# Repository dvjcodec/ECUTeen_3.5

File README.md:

# ECUTeen_3.5 rev.A (not tested!)

Stand Alone ECU with Teensy 3.5

On the board:
- 4 injection chanels
- 4 ignition chanels (for active coils)
- 2 high current PWM chanels
- IDLE out
- BOOST out
- stepper motor 
- 3x low current outs (FAN, FUEL, LC1)
- BlueTooth connector
- Clutch control
- tachometer out
- 5V power supply with LM2596
- 2x O2 sensor input
- CAN
- inlet air temperature sensor input
- coolant temperature sensor input
- throttle position sensor input
- 2x HALL input or VR
- MAP sensor 3bar

## Firmware

Designed for firmware
[Speeduino](https://speeduino.com/forum/viewtopic.php?f=13&t=1593)

## License

[CC BY-NC 3.0](https://creativecommons.org/licenses/by-nc/3.0/)

## Authors

Krzysztof Dymianiuk @ Seaside Customs Garage
http://www.garage.seasidecustoms.com

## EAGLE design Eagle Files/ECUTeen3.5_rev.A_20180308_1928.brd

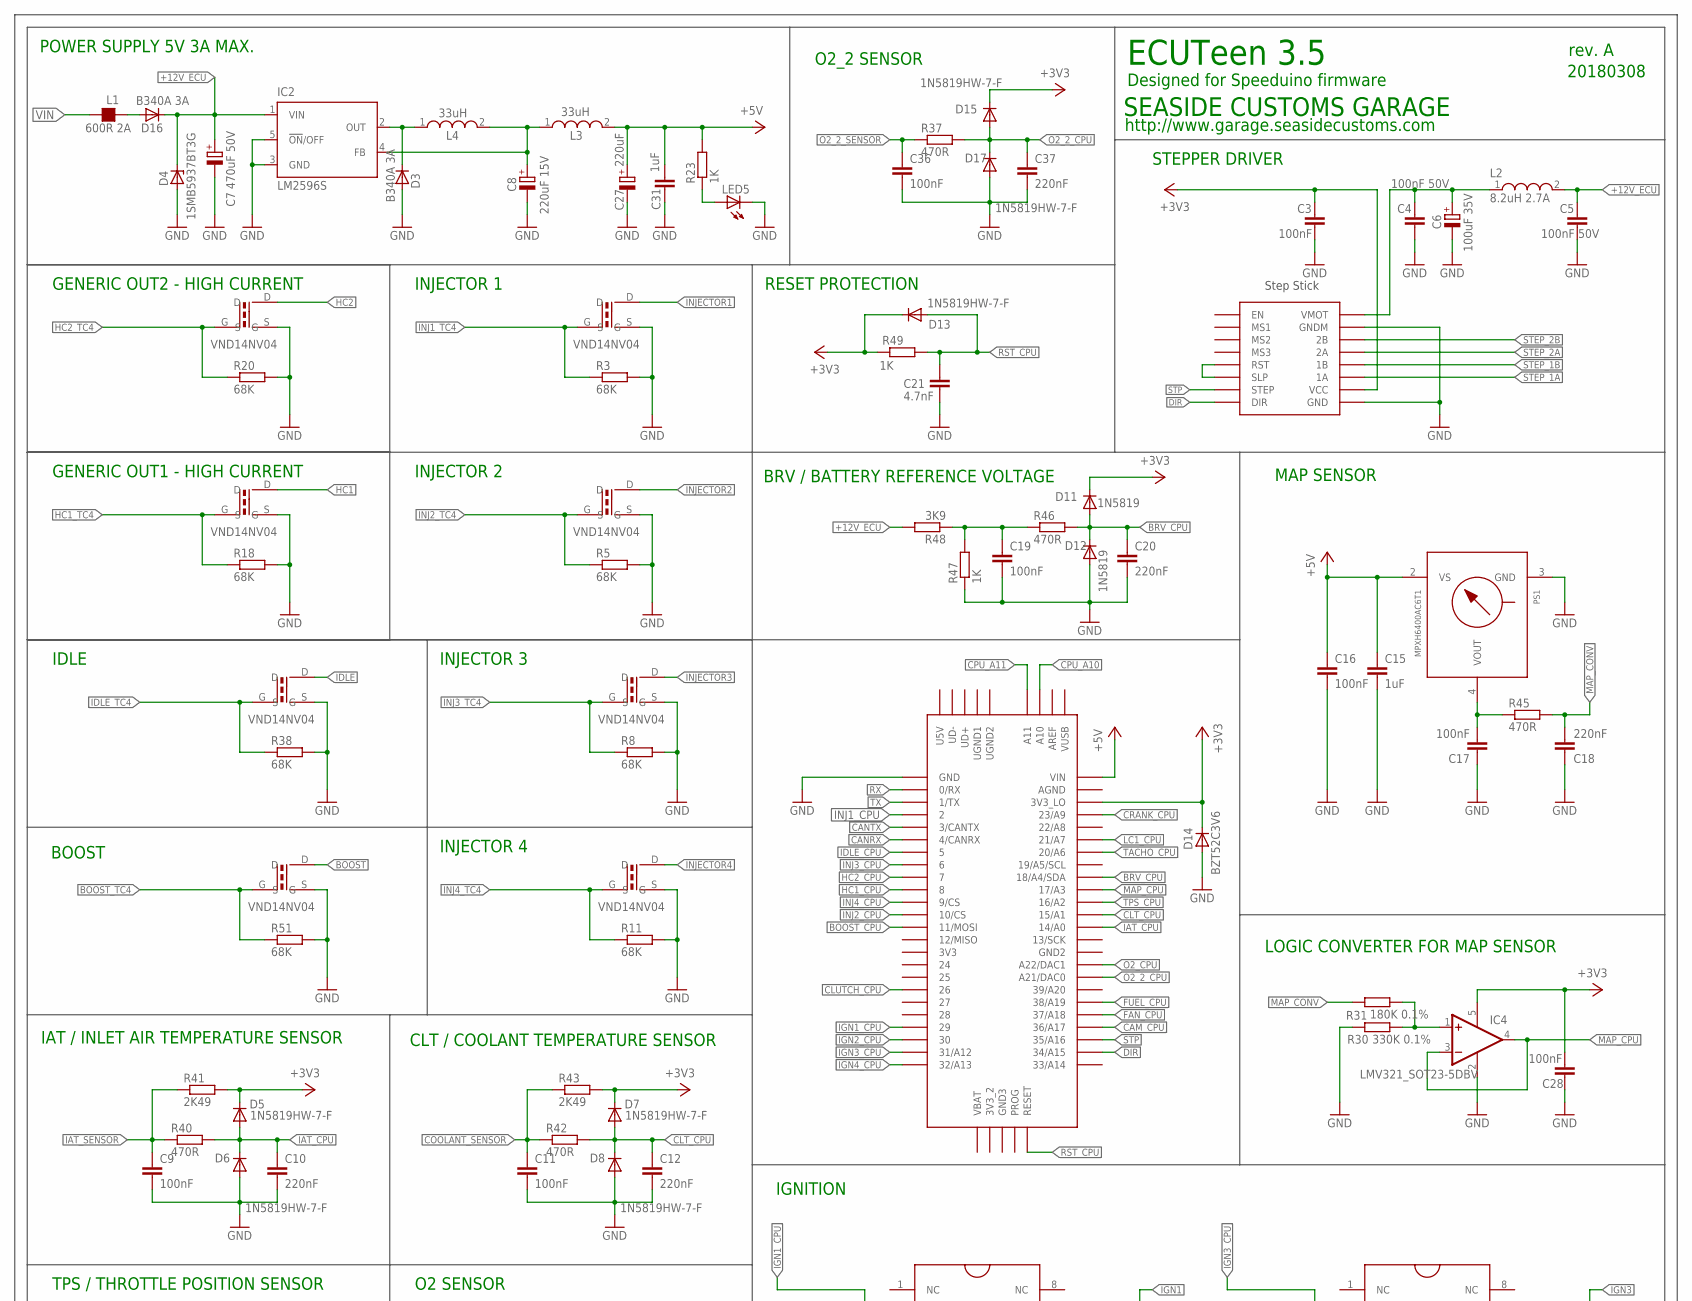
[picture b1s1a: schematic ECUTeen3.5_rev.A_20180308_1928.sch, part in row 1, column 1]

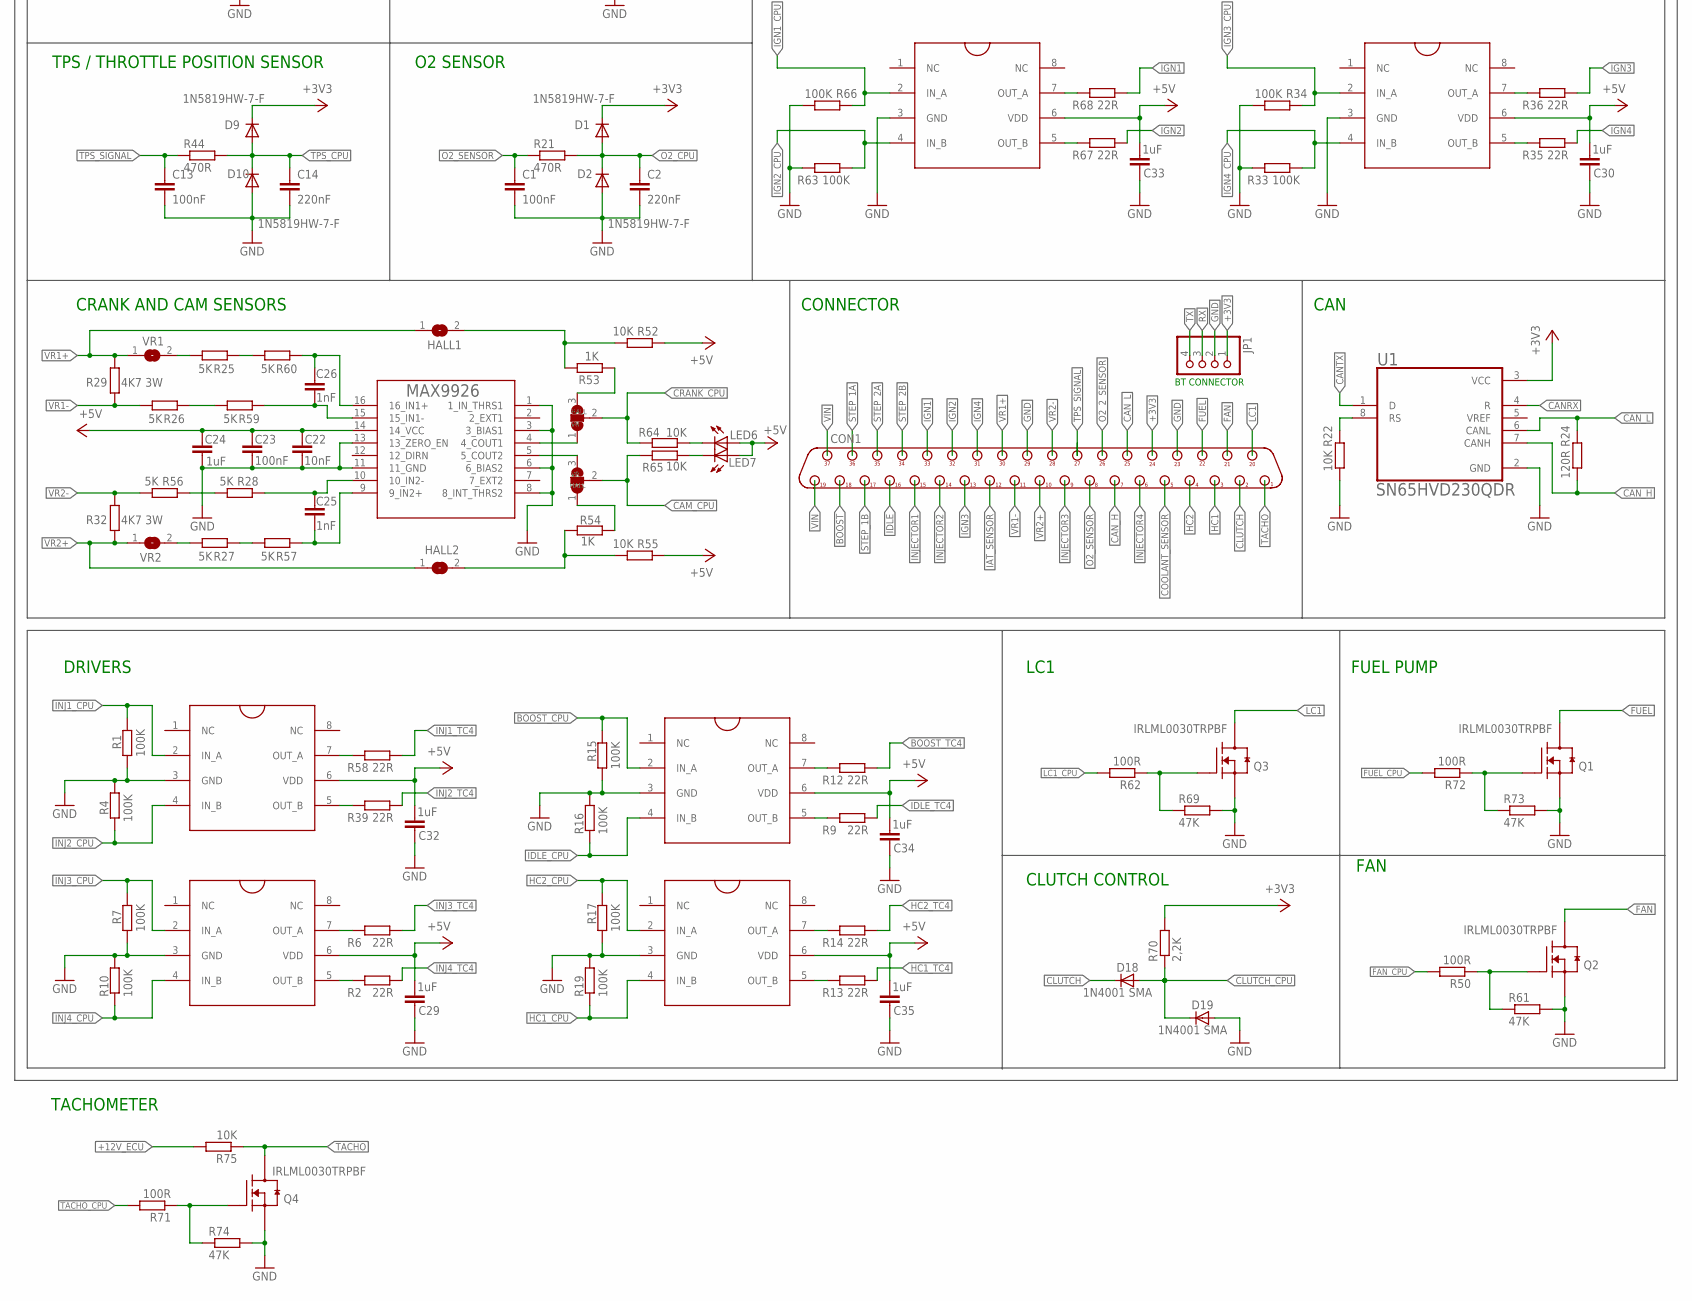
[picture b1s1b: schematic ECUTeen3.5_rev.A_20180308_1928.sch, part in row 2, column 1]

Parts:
C1, C3, C9, C11, C13, C16, C17, C19, C23, C28, C36: 100nF; C0805
C2, C10, C12, C14, C18, C20, C37: 220nF; C0805
C4, C5: 100nF 50V; C0805
C6: 100uF 35V; PANASONIC_D
C7: 470uF 50V; PANASONIC_D
C8: 220uF 15V; PANASONIC_D
C15, C24, C29, C30, C31, C32, C33, C34, C35: 1uF; C0805
C21: 4.7nF; C0805
C22: 10nF; C0805
C25, C26: 1nF; C0805
C27: 220uF; PANASONIC_D
CON1: DB37M/90; D-37M/90
D1, D2, D5, D6, D7, D8, D9, D10, D13, D15, D17: 1N5819HW-7-F; SOD123
D3, D16: B340A 3A; DO214AC
D4: 1SMB5937BT3G; SMB
D11, D12: 1N5819; SOD123
D14: BZT52C3V6; SOD123
D18, D19: 1N4001 SMA; DO214AC
IC2: LM2596S; TO263-5
IC4: LMV321_SOT23-5DBV; SOT23-5
JMP1, JMP2: SJ2W; SJ_2
JP1: PINHD-1X4; 1X04
L1: 600R 2A; L1206
L2: 8.2uH 2.7A; WE-PD_7332/7345_PLASTIC_BASE
L3, L4: 33uH; WE-LHMI_7030/7050
LED5, LED6, LED7: LEDCHIP-LED0805; CHIP-LED0805
PS1: MPXH6400AC6T1; 1317A
Q1, Q2, Q3, Q4: IRLML0030TRPBF; SOT95P280X135-3N
R1, R4, R7, R10, R15, R16, R17, R19, R33, R34, R63, R66: 100K; R0805
R2, R6, R9, R12, R13, R14, R39, R58: 22R; R0805
R3, R5, R8, R11, R18, R20, R38, R51: 68K; R0805
R21, R37, R40, R42, R44, R45, R46: 470R; R0805
R22, R52, R55, R64, R65, R75: 10K; R0805
R23, R47, R49, R53, R54: 1K; R0805
R24: 120R; R0805
R25, R26, R27, R28, R56, R57, R59, R60: 5K; R0805
R29, R32: 4K7 3W; R2512
R30: 330K 0.1%; R0805
R31: 180K 0.1%; R0805
R35, R36, R67, R68: 22R; M1206
R41, R43: 2K49; R0805
R48: 3K9; R0805
R50, R62, R71, R72: 100R; R0805
R61, R69, R73, R74: 47K; R0805
R70: 2,2K; R0805
SJ3: VR2; SJ
SJ4: VR1; SJ
SJ5: HALL2; SJ
SJ6: HALL1; SJ
STEPSTICK-X: STEP-STICK
U1: SN65HVD230QDR; SOIC127P600X175-8N
U$1: TEENSY_3.5/3.6
U$2, U$3, U$4, U$5, U$6, U$8, U$12, U$13: DPAK_N-CHANNEL_MOSFET
U$7, U$9, U$11, U$14, U$15, U$16: TC427SO-8; SO-8
U$10: MAX9926; QSOP16

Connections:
+3V3: C3.1, C28.2, CON1.24, D1.C, D5.C, D7.C, D9.C, D11.C, D13.C, D14.C, D15.C, IC4.5 (V+), JP1.1, R41.2, R43.2, R49.1, R70.2, STEPSTICK-X.VCC, U1.3 (VCC), U$1.3V3_LO
+5V: C15.1, C16.1, C22.1, C23.1, C24.1, C27.+, C29.2, C30.2, C31.1, C32.2, C33.2, C34.2, C35.2, L3.2, LED6.A, LED7.A, PS1.2 (VS), R23.2, R52.1, R55.1, U$1.VIN, U$7.6 (VDD), U$9.6 (VDD), U$10.14 (14_VCC), U$11.6 (VDD), U$14.6 (VDD), U$15.6 (VDD), U$16.6 (VDD)
+12V_ECU: C5.1, C7.+, D4.C, D16.C, IC2.1 (VIN), L2.2, R48.2, R75.2
BOOST: CON1.18, U$13.D
BOOST_CPU: R15.2, U$1.11/MOSI, U$15.2 (IN_A)
BOOST_TC4: R12.2, R51.1, U$13.G
BRV_CPU: C20.1, D11.A, D12.C, R46.2, U$1.18/A4/SDA
CAM_CPU: JMP2.2, R65.1, U$1.36/A17
CANRX: U1.4 (R), U$1.4/CANRX
CANTX: U1.1 (D), U$1.3/CANTX
CAN_H: CON1.7, R24.2, U1.7 (CANH)
CAN_L: CON1.25, R24.1, U1.6 (CANL)
CLT_CPU: C12.1, D7.A, D8.C, R42.2, U$1.15/A1
CLUTCH: CON1.2, D18.C
CLUTCH_CPU: D18.A, D19.C, R70.1, U$1.26
COOLANT_SENSOR: C11.1, CON1.5, R42.1, R43.1
CPU_A10: U$1.A10
CPU_A11: U$1.A11
CRANK_CPU: JMP1.2, R64.1, U$1.23/A9
DIR: STEPSTICK-X.DIR, U$1.34/A15
FAN: CON1.21, Q2.3 (D)
FAN_CPU: R50.2, U$1.37/A18
FUEL: CON1.22, Q1.3 (D)
FUEL_CPU: R72.2, U$1.38/A19
GND: C1.2, C2.2, C3.2, C4.2, C5.2, C6.-, C7.-, C8.-, C9.2, C10.2, C11.2, C12.2, C13.2, C14.2, C15.2, C16.2, C17.1, C18.1, C19.2, C20.2, C21.2, C22.2, C23.2, C24.2, C27.-, C28.1, C29.1, C30.1, C31.2, C32.1, C33.1, C34.1, C35.1, C36.2, C37.2, CON1.23, CON1.29, D2.A, D3.A, D4.A, D6.A, D8.A, D10.A, D12.A, D14.A, D17.A, D19.A, IC2.3 (GND), IC2.5 (!ON!/OFF), IC4.2 (V-), JP1.2, LED5.C, PS1.3 (GND), Q1.2 (S), Q2.2 (S), Q3.2 (S), Q4.2 (S), R1.1, R3.2, R4.1, R5.2, R7.1, R8.2, R10.1, R11.2, R15.1, R16.1, R17.1, R18.2, R19.1, R20.2, R22.2, R30.1, R33.1, R34.2, R38.2, R47.1, R51.2, R61.2, R63.1, R66.2, R69.2, R73.2, R74.2, STEPSTICK-X.GND, STEPSTICK-X.GNDM, U1.2 (GND), U$1.GND, U$2.S, U$3.S, U$4.S, U$5.S, U$6.S, U$7.3 (GND), U$8.S, U$9.3 (GND), U$10.1 (1_IN_THRS1), U$10.3 (3_BIAS1), U$10.6 (6_BIAS2), U$10.8 (8_INT_THRS2), U$10.11 (11_GND), U$10.13 (13_ZERO_EN), U$11.3 (GND), U$12.S, U$13.S, U$14.3 (GND), U$15.3 (GND), U$16.3 (GND)
HC1: CON1.3, U$3.D
HC1_CPU: R19.2, U$1.8, U$16.4 (IN_B)
HC1_TC4: R13.2, R18.1, U$3.G
HC2: CON1.4, U$2.D
HC2_CPU: R17.2, U$1.7, U$16.2 (IN_A)
HC2_TC4: R14.2, R20.1, U$2.G
IAT_CPU: C10.1, D5.A, D6.C, R40.2, U$1.14/A0
IAT_SENSOR: C9.1, CON1.12, R40.1, R41.1
IDLE: CON1.16, U$5.D
IDLE_CPU: R16.2, U$1.5, U$15.4 (IN_B)
IDLE_TC4: R9.2, R38.1, U$5.G
IGN1: CON1.33, R68.2
IGN1_CPU: R66.1, U$1.29, U$9.2 (IN_A)
IGN2: CON1.32, R67.2
IGN2_CPU: R63.2, U$1.30, U$9.4 (IN_B)
IGN3: CON1.13, R36.2
IGN3_CPU: R34.1, U$1.31/A12, U$11.2 (IN_A)
IGN4: CON1.31, R35.2
IGN4_CPU: R33.2, U$1.32/A13, U$11.4 (IN_B)
INJ1_CPU: R1.2, U$1.2, U$14.2 (IN_A)
INJ1_TC4: R3.1, R58.2, U$12.G
INJ2_CPU: R4.2, U$1.10/CS, U$14.4 (IN_B)
INJ2_TC4: R5.1, R39.2, U$4.G
INJ3_CPU: R7.2, U$1.6, U$7.2 (IN_A)
INJ3_TC4: R6.2, R8.1, U$6.G
INJ4_CPU: R10.2, U$1.9/CS, U$7.4 (IN_B)
INJ4_TC4: R2.2, R11.1, U$8.G
INJECTOR1: CON1.15, U$12.D
INJECTOR2: CON1.14, U$4.D
INJECTOR3: CON1.9, U$6.D
INJECTOR4: CON1.6, U$8.D
LC1: CON1.20, Q3.3 (D)
LC1_CPU: R62.2, U$1.21/A7
MAP_CONV: C18.2, R31.2, R45.2
MAP_CPU: IC4.3 (-IN), IC4.4 (OUT), U$1.17/A3
unnamed: JMP1.1, U$10.4 (4_COUT1)
unnamed: JMP1.3, R53.2
unnamed: R67.1, U$9.5 (OUT_B)
unnamed: JMP2.3, U$10.5 (5_COUT2)
unnamed: R68.1, U$9.7 (OUT_A)
unnamed: R35.1, U$11.5 (OUT_B)
unnamed: JMP2.1, R54.1
unnamed: R36.1, U$11.7 (OUT_A)
unnamed: Q2.1 (G), R50.1, R61.1
unnamed: R2.1, U$7.5 (OUT_B)
unnamed: Q3.1 (G), R62.1, R69.1
unnamed: R22.1, U1.8 (RS)
unnamed: STEPSTICK-X.RST, STEPSTICK-X.SLP
unnamed: C4.1, C6.+, L2.1, STEPSTICK-X.VMOT
unnamed: IC4.1 (+IN), R30.2, R31.1
unnamed: C19.1, R46.1, R47.2, R48.1
unnamed: R54.2, R55.2, SJ5.2
unnamed: Q4.1 (G), R71.1, R74.1
unnamed: C17.2, PS1.4 (VOUT), R45.1
unnamed: R52.2, R53.1, SJ6.2
unnamed: C25.2, R57.1, U$10.9 (9_IN2+)
unnamed: C26.1, R60.1, U$10.16 (16_IN1+)
unnamed: C26.2, R59.1, U$10.15 (15_IN1-)
unnamed: C25.1, R28.1, U$10.10 (10_IN2-)
unnamed: R25.1, R60.2
unnamed: R27.2, SJ3.2
unnamed: R25.2, SJ4.2
unnamed: LED7.C, R65.2
unnamed: LED6.C, R64.2
unnamed: D16.A, L1.1
unnamed: R6.1, U$7.7 (OUT_A)
unnamed: R9.1, U$15.5 (OUT_B)
unnamed: LED5.A, R23.1
unnamed: R26.1, R59.2
unnamed: R27.1, R57.2
unnamed: R28.2, R56.1
unnamed: R12.1, U$15.7 (OUT_A)
unnamed: R13.1, U$16.5 (OUT_B)
unnamed: R39.1, U$14.5 (OUT_B)
unnamed: R14.1, U$16.7 (OUT_A)
unnamed: R58.1, U$14.7 (OUT_A)
unnamed: Q1.1 (G), R72.1, R73.1
unnamed: D3.C, IC2.2 (OUT), L4.1
O2_2_CPU: C37.1, D15.A, D17.C, R37.2, U$1.21/DAC0 (A21/DAC0)
O2_2_SENSOR: C36.1, CON1.26, R37.1
O2_CPU: C2.1, D1.A, D2.C, R21.2, U$1.A22/DAC1
O2_SENSOR: C1.1, CON1.8, R21.1
RST_CPU: C21.1, D13.A, R49.2, U$1.RESET
RX: JP1.3, U$1.0/RX
STEP_1A: CON1.36, STEPSTICK-X.1A
STEP_1B: CON1.17, STEPSTICK-X.1B
STEP_2A: CON1.35, STEPSTICK-X.2A
STEP_2B: CON1.34, STEPSTICK-X.2B
STP: STEPSTICK-X.SPT (STEP), U$1.35/A16
SUPP1: C8.+, IC2.4 (FB), L3.1, L4.2
TACHO: CON1.1, Q4.3 (D), R75.1
TACHO_CPU: R71.2, U$1.20/A6
TPS_CPU: C14.1, D9.A, D10.C, R44.2, U$1.16/A2
TPS_SIGNAL: C13.1, CON1.27, R44.1
TX: JP1.4, U$1.1/TX
VIN: CON1.19, CON1.37, L1.2
VR1+: CON1.30, R29.1, SJ4.1, SJ6.1
VR1-: CON1.11, R26.2, R29.2
VR2+: CON1.10, R32.2, SJ3.1, SJ5.1
VR2-: CON1.28, R32.1, R56.2

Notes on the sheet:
INJECTOR 1
INJECTOR 2
INJECTOR 3
INJECTOR 4
BOOST
IDLE
GENERIC OUT1 - HIGH CURRENT
GENERIC OUT2 - HIGH CURRENT
O2 SENSOR
POWER SUPPLY 5V 3A MAX.
STEPPER DRIVER
ECUTeen 3.5
Designed for Speeduino firmware
rev. A
20180308
SEASIDE CUSTOMS GARAGE
http://www.garage.seasidecustoms.com
IAT / INLET AIR TEMPERATURE SENSOR
CLT / COOLANT TEMPERATURE SENSOR
TPS / THROTTLE POSITION SENSOR
MAP SENSOR
LOGIC CONVERTER FOR MAP SENSOR
BRV / BATTERY REFERENCE VOLTAGE
RESET PROTECTION
CRANK AND CAM SENSORS
CONNECTOR
IGNITION
HALL
DRIVERS
CAN
O2_2 SENSOR
BT CONNECTOR
FUEL PUMP
FAN
LC1
CLUTCH CONTROL
TACHOMETER

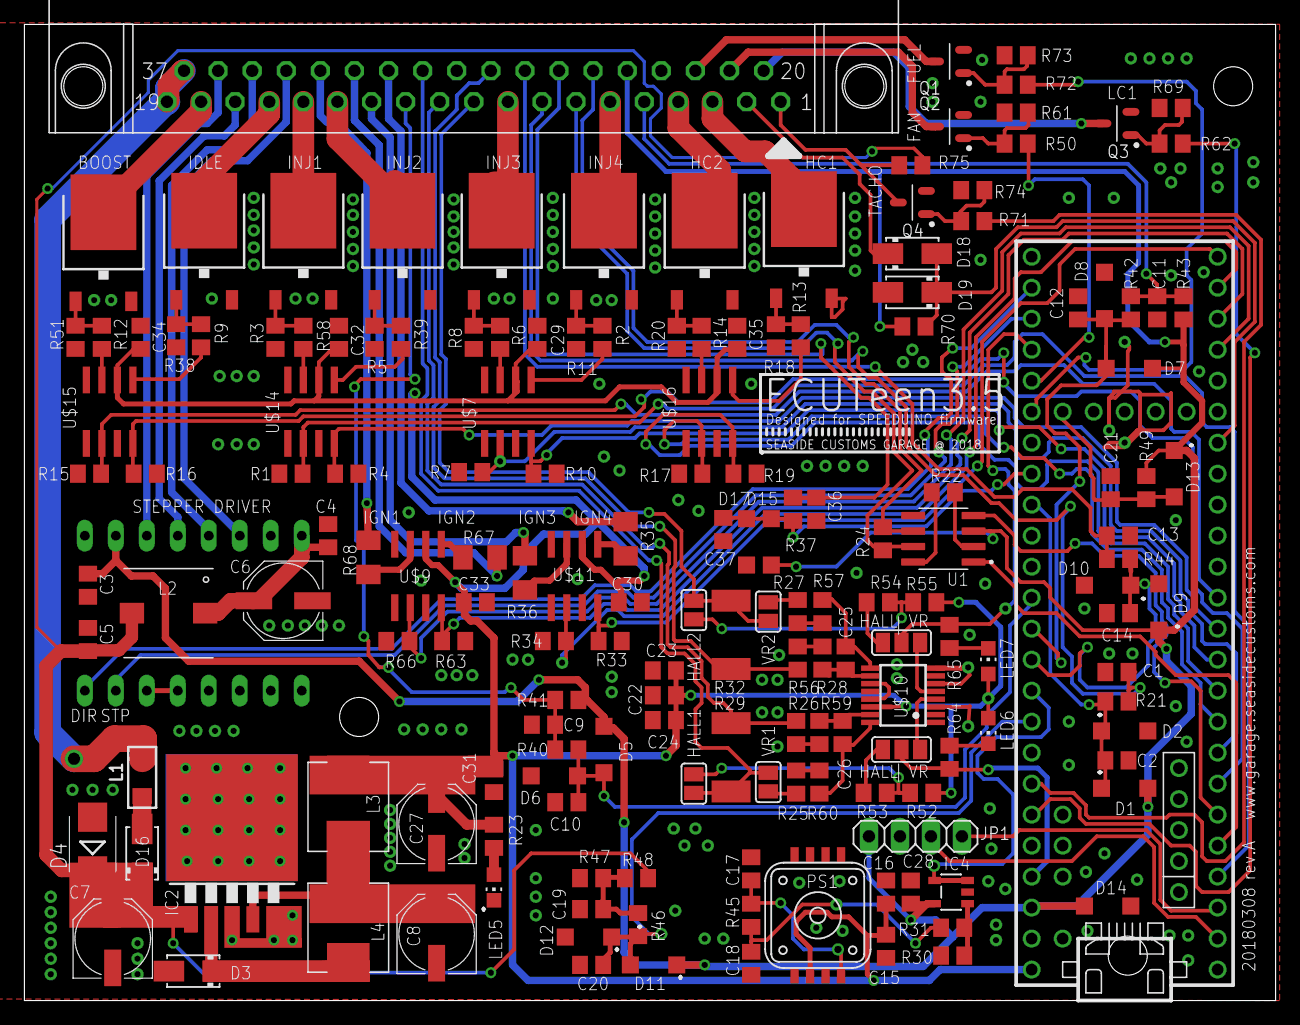
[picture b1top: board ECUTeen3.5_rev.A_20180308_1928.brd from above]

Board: 2 copper layers, 102.5 x 80.0 mm, 171 parts (0 on the bottom side), 123 nets.

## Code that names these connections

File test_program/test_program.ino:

// Simple "blinking LED's" program to test outputs 
// Krzysztof Dymianiuk @ Seaside Customs Garage

int led = 29;   //Ignition1
int led2 = 30;  //Ignition2
int led3 = 31;  //Ignition3
int led4 = 32;  //Ignition4
int led5 = 13;  //LED on Teensy
int led6 = 2;   //injector1
int led7 = 10;  //injector2
int led8 = 6;   //injector3
int led9 = 9;   //injector4
int led10 = 8;   //HC1
int led11 = 7;   //HC2
int led12 = 11;  //Boost
int led13 = 5;   //Idle
int led14 = 21;  //LC1
int led15 = 38;  //Fuel pump
int led16 = 37;  //Fan control
int led17 = 20;  //Tacho out


void setup() {               
// initialize the digital pin as an output.
pinMode(led, OUTPUT);
pinMode(led2, OUTPUT);
pinMode(led3, OUTPUT); 
pinMode(led4, OUTPUT);
pinMode(led5, OUTPUT);
pinMode(led6, OUTPUT);
pinMode(led7, OUTPUT);
pinMode(led8, OUTPUT);
pinMode(led9, OUTPUT);
pinMode(led10, OUTPUT);
pinMode(led11, OUTPUT);
pinMode(led12, OUTPUT);
pinMode(led13, OUTPUT);
pinMode(led14, OUTPUT);
pinMode(led15, OUTPUT);
pinMode(led16, OUTPUT);
pinMode(led17, OUTPUT);
}

void loop() 
{digitalWrite(led, HIGH);   // turn the LED on (HIGH is the voltage level)
delay(100);                 // wait for a second
digitalWrite(led, LOW);     // turn the LED off by making the voltage LOW
delay(100);                 // wait for a second

{digitalWrite(led2, HIGH);
delay(100);
digitalWrite(led2, LOW);
delay(100);}

{digitalWrite(led3, HIGH);
delay(100);
digitalWrite(led3, LOW);
delay(100);}

{digitalWrite(led4, HIGH);
delay(100);
digitalWrite(led4, LOW);
delay(100);}

{digitalWrite(led5, HIGH);
delay(100);
digitalWrite(led5, LOW);
delay(100);}

{digitalWrite(led6, HIGH);
delay(100);
digitalWrite(led6, LOW);
delay(100);}

{digitalWrite(led7, HIGH);
delay(100);
digitalWrite(led7, LOW);
delay(100);}

{digitalWrite(led8, HIGH);
delay(100);
digitalWrite(led8, LOW);
delay(100);}

{digitalWrite(led9, HIGH);
delay(100);
digitalWrite(led9, LOW);
delay(100);}

{digitalWrite(led10, HIGH);
delay(100);
digitalWrite(led10, LOW);
delay(100);}

{digitalWrite(led11, HIGH);
delay(100);
digitalWrite(led11, LOW);
delay(100);}

{digitalWrite(led12, HIGH);
delay(100);
digitalWrite(led12, LOW);
delay(100);}

{digitalWrite(led13, HIGH);
delay(100);
digitalWrite(led13, LOW);
delay(100);}

{digitalWrite(led14, HIGH);
delay(100);
digitalWrite(led14, LOW);
delay(100);}

{digitalWrite(led15, HIGH);
delay(100);
digitalWrite(led15, LOW);
delay(100);}

{digitalWrite(led16, HIGH);
delay(100);
digitalWrite(led16, LOW);
delay(100);}

{digitalWrite(led17, HIGH);
delay(100);
digitalWrite(led17, LOW);
delay(100);}

}

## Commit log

2018-04-05 Add files via upload
    Simple test program to check outputs via LED diode. If blinking - output is OK.
    For ignitions positive on pins, for rest outputs negative on pin.

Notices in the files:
parts and their libraries:
rc-master-smd: Copyright (C) 2007, Bob Starr
Wurth Passive: Copyright: Würth Elektronik
